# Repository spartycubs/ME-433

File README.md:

# ME-433
Advanced Mechatronics - Spring Quarter 2017

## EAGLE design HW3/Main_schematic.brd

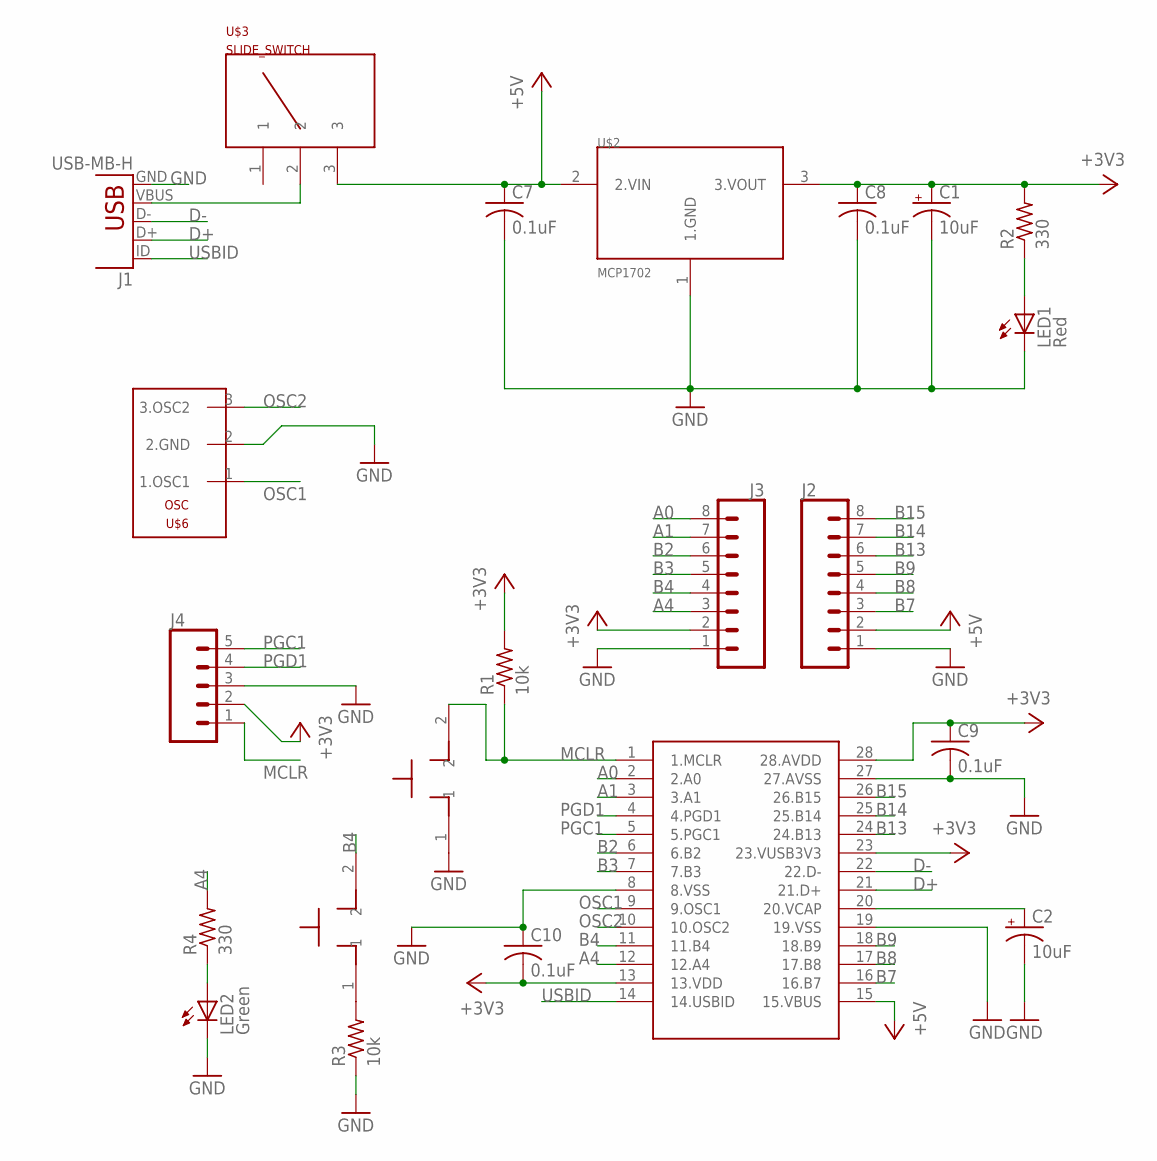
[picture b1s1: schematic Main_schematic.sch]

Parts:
C1, C2: 10uF; B45181B
C7, C8, C9, C10: 0.1uF; C025-024X044
J1: USB-MB-H
J2, J3: CONN_08"; 1X08
J4: CONN_05; 1X05
LED1: Red; LED3MM
LED2: Green; LED3MM
R1, R3: 10k; 0207/10
R2, R4: 330; 0207/10
U$1: PIC32MX250F128B; DIL28-3
U$2: MCP1702; TO92
U$3: SLIDE_SWITCH
U$4, U$5: PB
U$6: OSC

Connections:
+3V3: C1.+, C8.1, C9.1, C10.2, J3.2, J4.2, R1.2, R2.2, U$1.13 (13.VDD), U$1.23 (23.VUSB3V3), U$1.28 (28.AVDD), U$2.3 (3.VOUT)
+5V: C7.1, J2.2, U$1.15 (15.VBUS), U$2.2 (2.VIN), U$3.3
A0: J3.8, U$1.2 (2.A0)
A1: J3.7, U$1.3 (3.A1)
A4: J3.3, R4.2, U$1.12 (12.A4)
B2: J3.6, U$1.6 (6.B2)
B3: J3.5, U$1.7 (7.B3)
B4: J3.4, U$1.11 (11.B4), U$5.2
B7: J2.3, U$1.16 (16.B7)
B8: J2.4, U$1.17 (17.B8)
B9: J2.5, U$1.18 (18.B9)
B13: J2.6, U$1.24 (24.B13)
B14: J2.7, U$1.25 (25.B14)
B15: J2.8, U$1.26 (26.B15)
D+: J1.D+, U$1.21 (21.D+)
D-: J1.D-, U$1.22 (22.D-)
GND: C1.-, C2.-, C7.2, C8.2, C9.2, C10.1, J1.GND, J2.1, J3.1, J4.3, LED1.K (C), LED2.K (C), R3.1, U$1.8 (8.VSS), U$1.19 (19.VSS), U$1.27 (27.AVSS), U$2.1 (1.GND), U$4.1, U$6.2 (2.GND)
MCLR: J4.1, R1.1, U$1.1 (1.MCLR), U$4.2
unnamed: R3.2, U$5.1
unnamed: C2.+, U$1.20 (20.VCAP)
unnamed: LED2.A, R4.1
unnamed: LED1.A, R2.1
unnamed: J1.VBUS, U$3.2
OSC1: U$1.9 (9.OSC1), U$6.1 (1.OSC1)
OSC2: U$1.10 (10.OSC2), U$6.3 (3.OSC2)
PGC1: J4.5, U$1.5 (5.PGC1)
PGD1: J4.4, U$1.4 (4.PGD1)
USBID: J1.ID, U$1.14 (14.USBID)

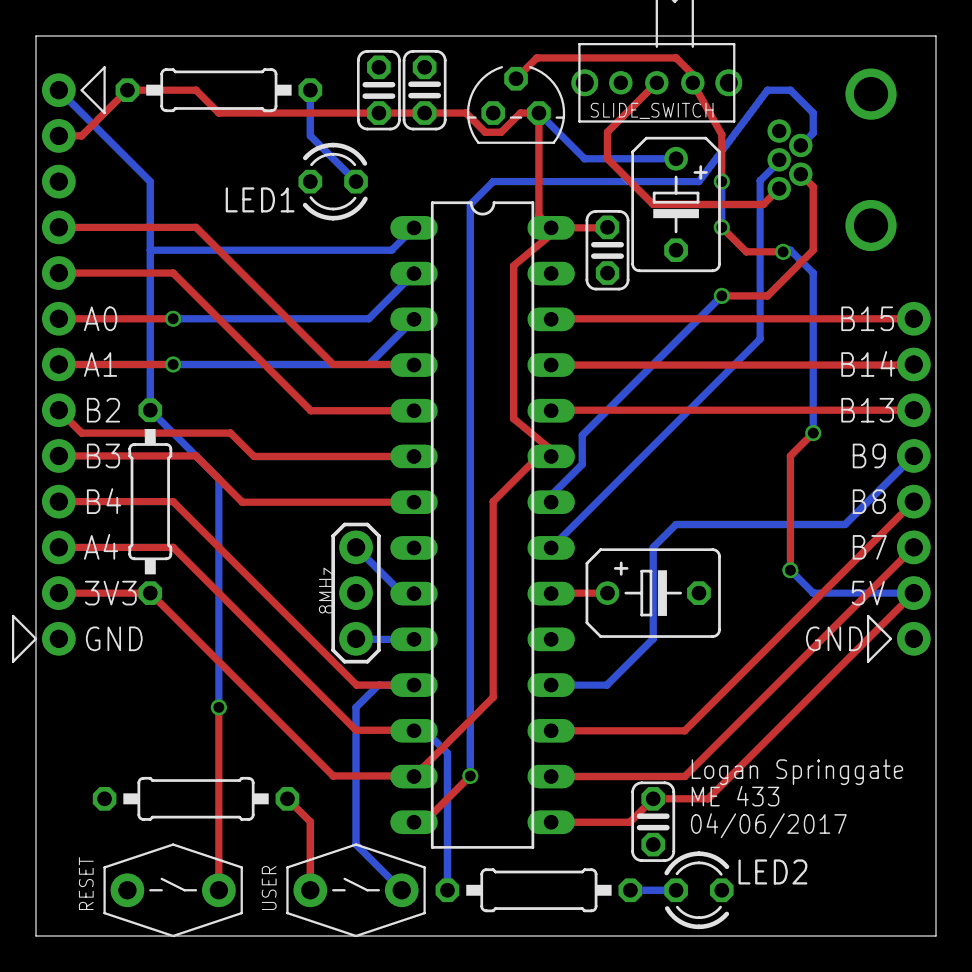
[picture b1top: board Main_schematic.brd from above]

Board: 2 copper layers, 50.0 x 50.0 mm, 22 parts (0 on the bottom side), 28 nets.

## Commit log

2017-04-11 Added HW2 to GitHub
2017-04-11 Added all files
2017-04-11 Debugging changes
2017-04-13 Updated files
2017-04-13 Fixed GitHub desktop
    Files sync correctly now
2017-04-13 I2C1 changed to I2C2
2017-04-13 Started pin setup
2017-04-17 Added I2C read and write functions
2017-04-18 It almost works
2017-04-18 Still not working
2017-04-18 Began LCD homework
2017-04-20 Can write to LCD screen
2017-04-20 writing to LCD screen
    Cannot live update still
2017-04-23 Counter and bar now working
2017-04-23 Finished
2017-04-23 Trying to fix SPI files
2017-04-23 Still not functional
2017-04-25 Accelerometer might be broken
2017-05-04 IMU Finished
2017-05-04 File management changes
2017-05-04 Harmony is working
2017-05-18 Starting USB
2017-06-02 HW12 - Slider Bar
2017-06-02 went back and fixed SPI finally
2017-06-02 HW4 Done
2017-06-02 File management
2017-06-02 I2C still not working
2017-06-02 Added SPI video
2017-06-05 Started USB communication
2017-06-05 USB HW9 Done
2017-06-06 DSP mostly done
2017-06-07 Mouse not working, Camera App done
2017-06-07 Android USB code finished
2017-06-07 Mouse worksish
2017-06-08 HW14
2017-06-08 Create HW15
2017-06-08 CAD Files
2017-06-08 Laser Cutting
